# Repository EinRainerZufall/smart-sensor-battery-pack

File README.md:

# Smart Sensor Battery Pack
This is the experimental battery charging PCB designed for my YouTube video. You can see the full build process, design theory, and assembly in the video below:

### Please note: 
This board is currently missing a pull up resistor on the SCL/SDA lines - I will be adding this very soon. Software correction is possible using the XIAO pull-ups, and closing the FET early in the boot cycle. So using the board in its current form just makes the code a little more verbose. 

```
# Force GPIO18 LOW (Turns P-Channel MOSFET on)
# Set priority such that this runs before i2c initialises
esphome:
  on_boot:
    - priority: 1200
      then:
        - lambda: |-
            gpio_config_t io_conf = {};
            io_conf.pin_bit_mask = (1ULL<<18);
            io_conf.mode = GPIO_MODE_OUTPUT;
            io_conf.pull_up_en = GPIO_PULLUP_DISABLE;
            io_conf.pull_down_en = GPIO_PULLDOWN_DISABLE;
            io_conf.intr_type = GPIO_INTR_DISABLE;
            gpio_config(&io_conf);
            gpio_set_level(GPIO_NUM_18, 0);

# Software accessible pullups
i2c:
  sda_pullup_enabled: true
  scl_pullup_enabled: true

```

## ⚠️ Safety Warning
This board involves **Lithium-Ion battery charging**. 
*   This is an **experimental prototype** from a hobbyist. **I am not a professional engineer**. It has **not** been certified by safety agencies (UL, CE, etc.).
*   Lithium batteries can be dangerous if mishandled (risk of thermal runaway, fire, explosion, and serious injury).
*   **DO NOT leave this device unattended with a battery connected**
*   By using these files, you agree that you are solely responsible for verifying the safety of the circuit.

## License & Liability

### 1. Non-Commercial Use Only
This project is shared under the [Creative Commons Attribution-NonCommercial-ShareAlike 4.0 International](https://creativecommons.org/licenses/by-nc-sa/4.0/) license.
*  **You are free to:** Download, modify, and build this for personal use or learning.
*  **You may NOT:** Sell this board, use it in a product you sell, or use these files for any commercial purpose.
*  If you modify and share this design, you must share it under this same license.

### 2. No Liability (Disclaimer)
These files are provided "As Is" for educational purposes ONLY. I am sharing my personal project notes. **I accept no liability for any damage, injury, or loss** that occurs from the use or assembly of these files. Use them at your own risk.

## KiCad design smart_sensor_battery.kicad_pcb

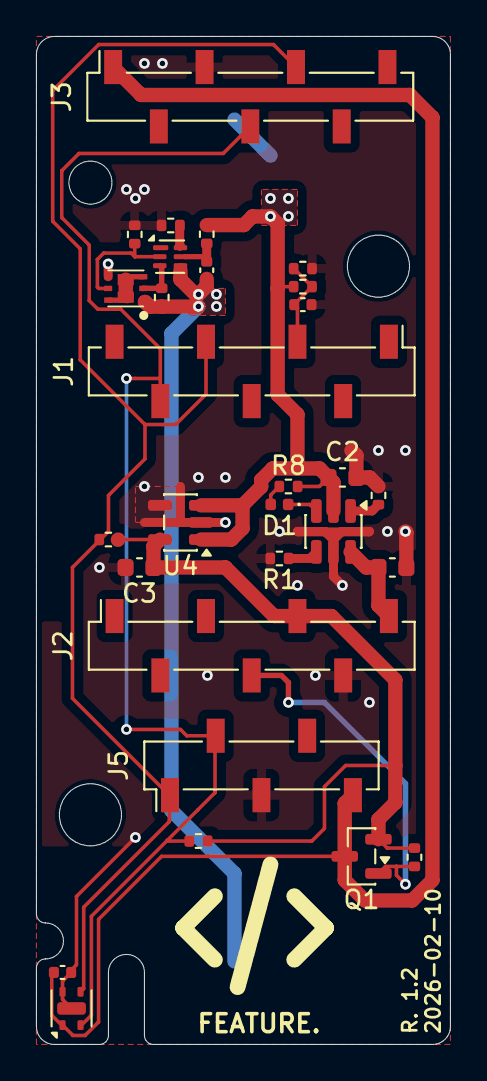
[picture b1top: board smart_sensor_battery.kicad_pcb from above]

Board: 2 copper layers, 23.0 x 56.0 mm, 30 parts (1 on the bottom side), 19 nets.

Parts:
BT1: 1096; BAT_1096
C1, C2, C3: 2.2uF@16v; C_0603_1608Metric
C4, C5, C6: 100nF@16v; C_0402_1005Metric
D1: LED; LED_0402_1005Metric
J1: Upper MCU Socket; PinSocket_1x07_P2.54mm_Vertical_SMD_Pin1Left
J2: Lower MCU Socket; PinSocket_1x07_P2.54mm_Vertical_SMD_Pin1Right
J3: Sensor Socket; PinSocket_1x07_P2.54mm_Vertical_SMD_Pin1Right
J5: 5-pin Socket; PinSocket_1x05_P2.54mm_Vertical_SMD_Pin1Left
Q1: AO3401A; SOT-23
R1: 1.2k; R_0402_1005Metric
R2: 10k; R_0402_1005Metric
R3, R8: 2.2k; R_0402_1005Metric
R4: 330; R_0402_1005Metric
R5, R6, R11, R12: 5.1M; R_0402_1005Metric
R7: 100k; R_0402_1005Metric
R9, R10: 3k3; R_0402_1005Metric
U2: BQ21040DBV; SOT-23-6
U4: TPS7A0533PDBV; SOT-23-5
U5: BQ29700; WSON-6_1.5x1.5mm_P0.5mm
U6: CSD85301Q2
U7: SHTC3; Sensirion_DFN-4-1EP_2x2mm_P1mm_EP0.7x1.6mm

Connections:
+3V3: C3.1, J2.5, Q1.2 (S), R7.2, R9.1, R10.1, U4.5 (OUT)
/3V3_{SW}: C5.1, J3.1, J5.5, Q1.3 (D), U7.1 (VDD)
/BAT+: C2.1, R4.2, R8.2, R12.1, U2.2 (OUT), U4.1 (IN), U4.3 (EN)
/BAT-: BT1.N, C4.2, R6.1, U5.4 (VSS), U6.1 (S1)
/BAT_{SENSE}: C6.1, J1.3, R11.1, R12.2
/MOSFET_{DRAIN}: U6.3 (D2), U6.6 (D1), U6.7 (D1), U6.8 (D2)
/SCL: J1.6, J3.4, J5.2, R9.2, U7.2 (SCL)
/SDA: J1.5, J3.5, J5.1, R10.2, U7.3 (SDA)
/V_{USB}: C1.1, J2.7, U2.6 (VIN)
GND: C1.2, C2.2, C3.2, C5.2, C6.2, J2.6, J3.3, J5.3, R1.2, R2.2, R3.2, R5.2, R11.2, U2.5 (GND), U4.2 (GND), U4.4 (NC_(GND)), U6.4 (S2), U7.4 (VSS), U7.5 (GND_(centre_pad))
unnamed: D1.2 (A), R8.1
unnamed: D1.1 (K), U2.3 (~CHG)
unnamed: J2.4, Q1.1 (G), R7.1
unnamed: R1.1, U2.4 (ISET)
unnamed: R2.1, U2.1 (TS)
unnamed: C4.1, R4.1, U5.5 (BAT)
unnamed: R5.1, U5.2 (Cout), U6.5 (G2)
unnamed: R6.2, U5.3 (Dout), U6.2 (G1)
unnamed: R3.1, U5.6 (V-)

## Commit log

2026-02-12 move PCB files to a seperate folder
    update .gitignore
2026-03-22 update PCB
2026-03-22 add custom component for soil sensor
2026-03-22 remove csv
2026-03-22 add ESPHome yaml
2026-03-22 add measurement of the power consumption
